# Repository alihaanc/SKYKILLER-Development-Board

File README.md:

# SKYKILLER-Development-Board
Drone and Rocket Development PCB board

## Different Color

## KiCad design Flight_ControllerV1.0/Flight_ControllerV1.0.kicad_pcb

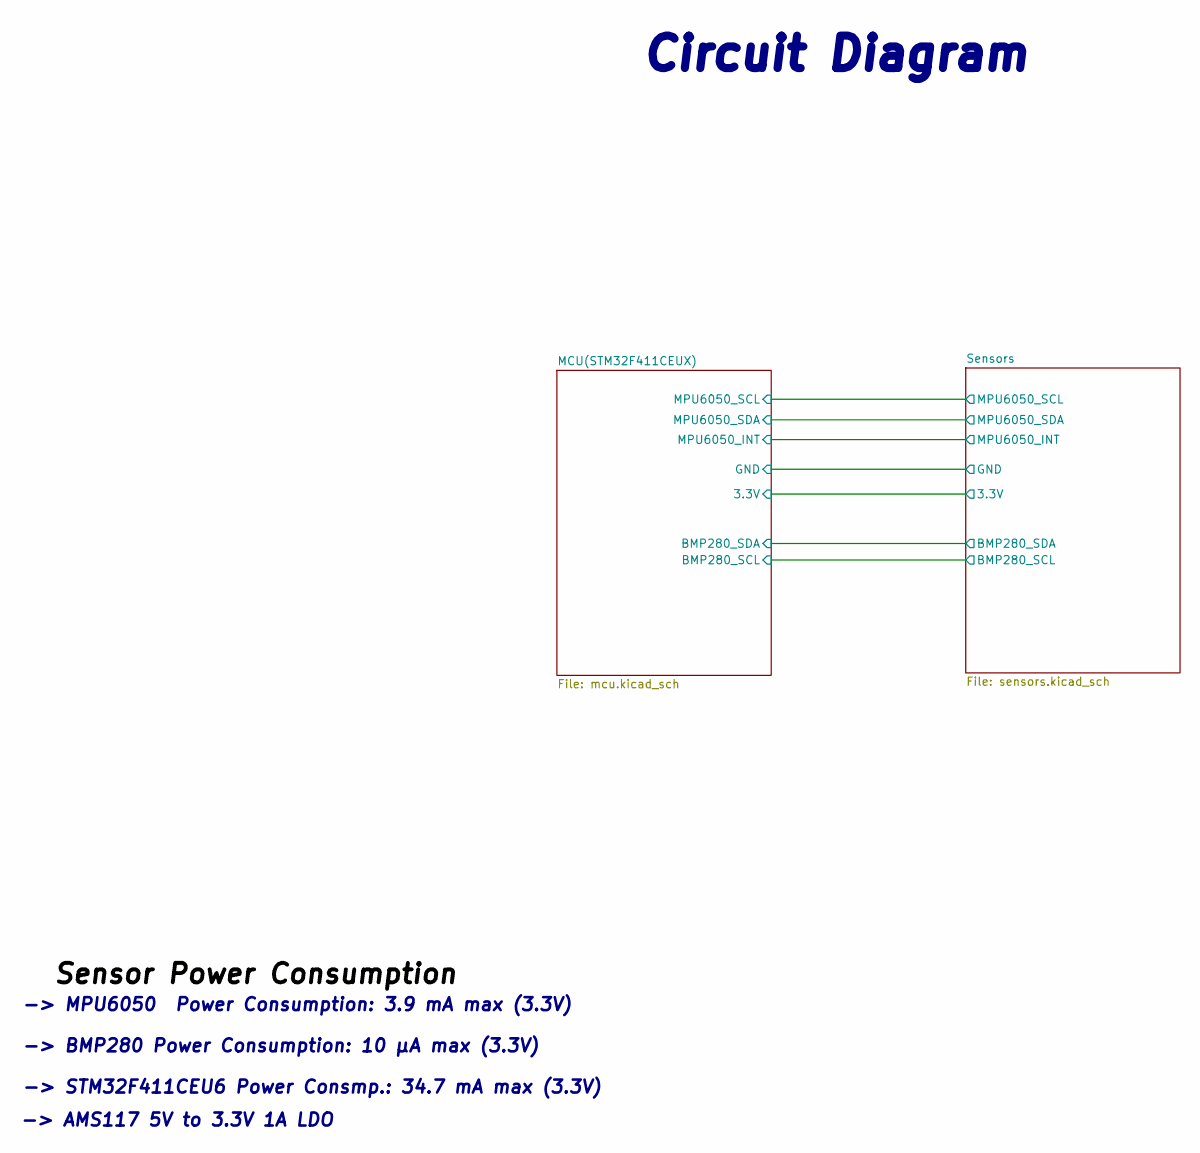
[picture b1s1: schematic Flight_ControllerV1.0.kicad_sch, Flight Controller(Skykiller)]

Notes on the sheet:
-> AMS117 5V to 3.3V 1A LDO
Circuit Diagram
-> MPU6050 Power Consumption: 3.9 mA max (3.3V)
-> BMP280 Power Consumption: 10 μA max (3.3V)
-> STM32F411CEU6 Power Consmp.: 34.7 mA max (3.3V)

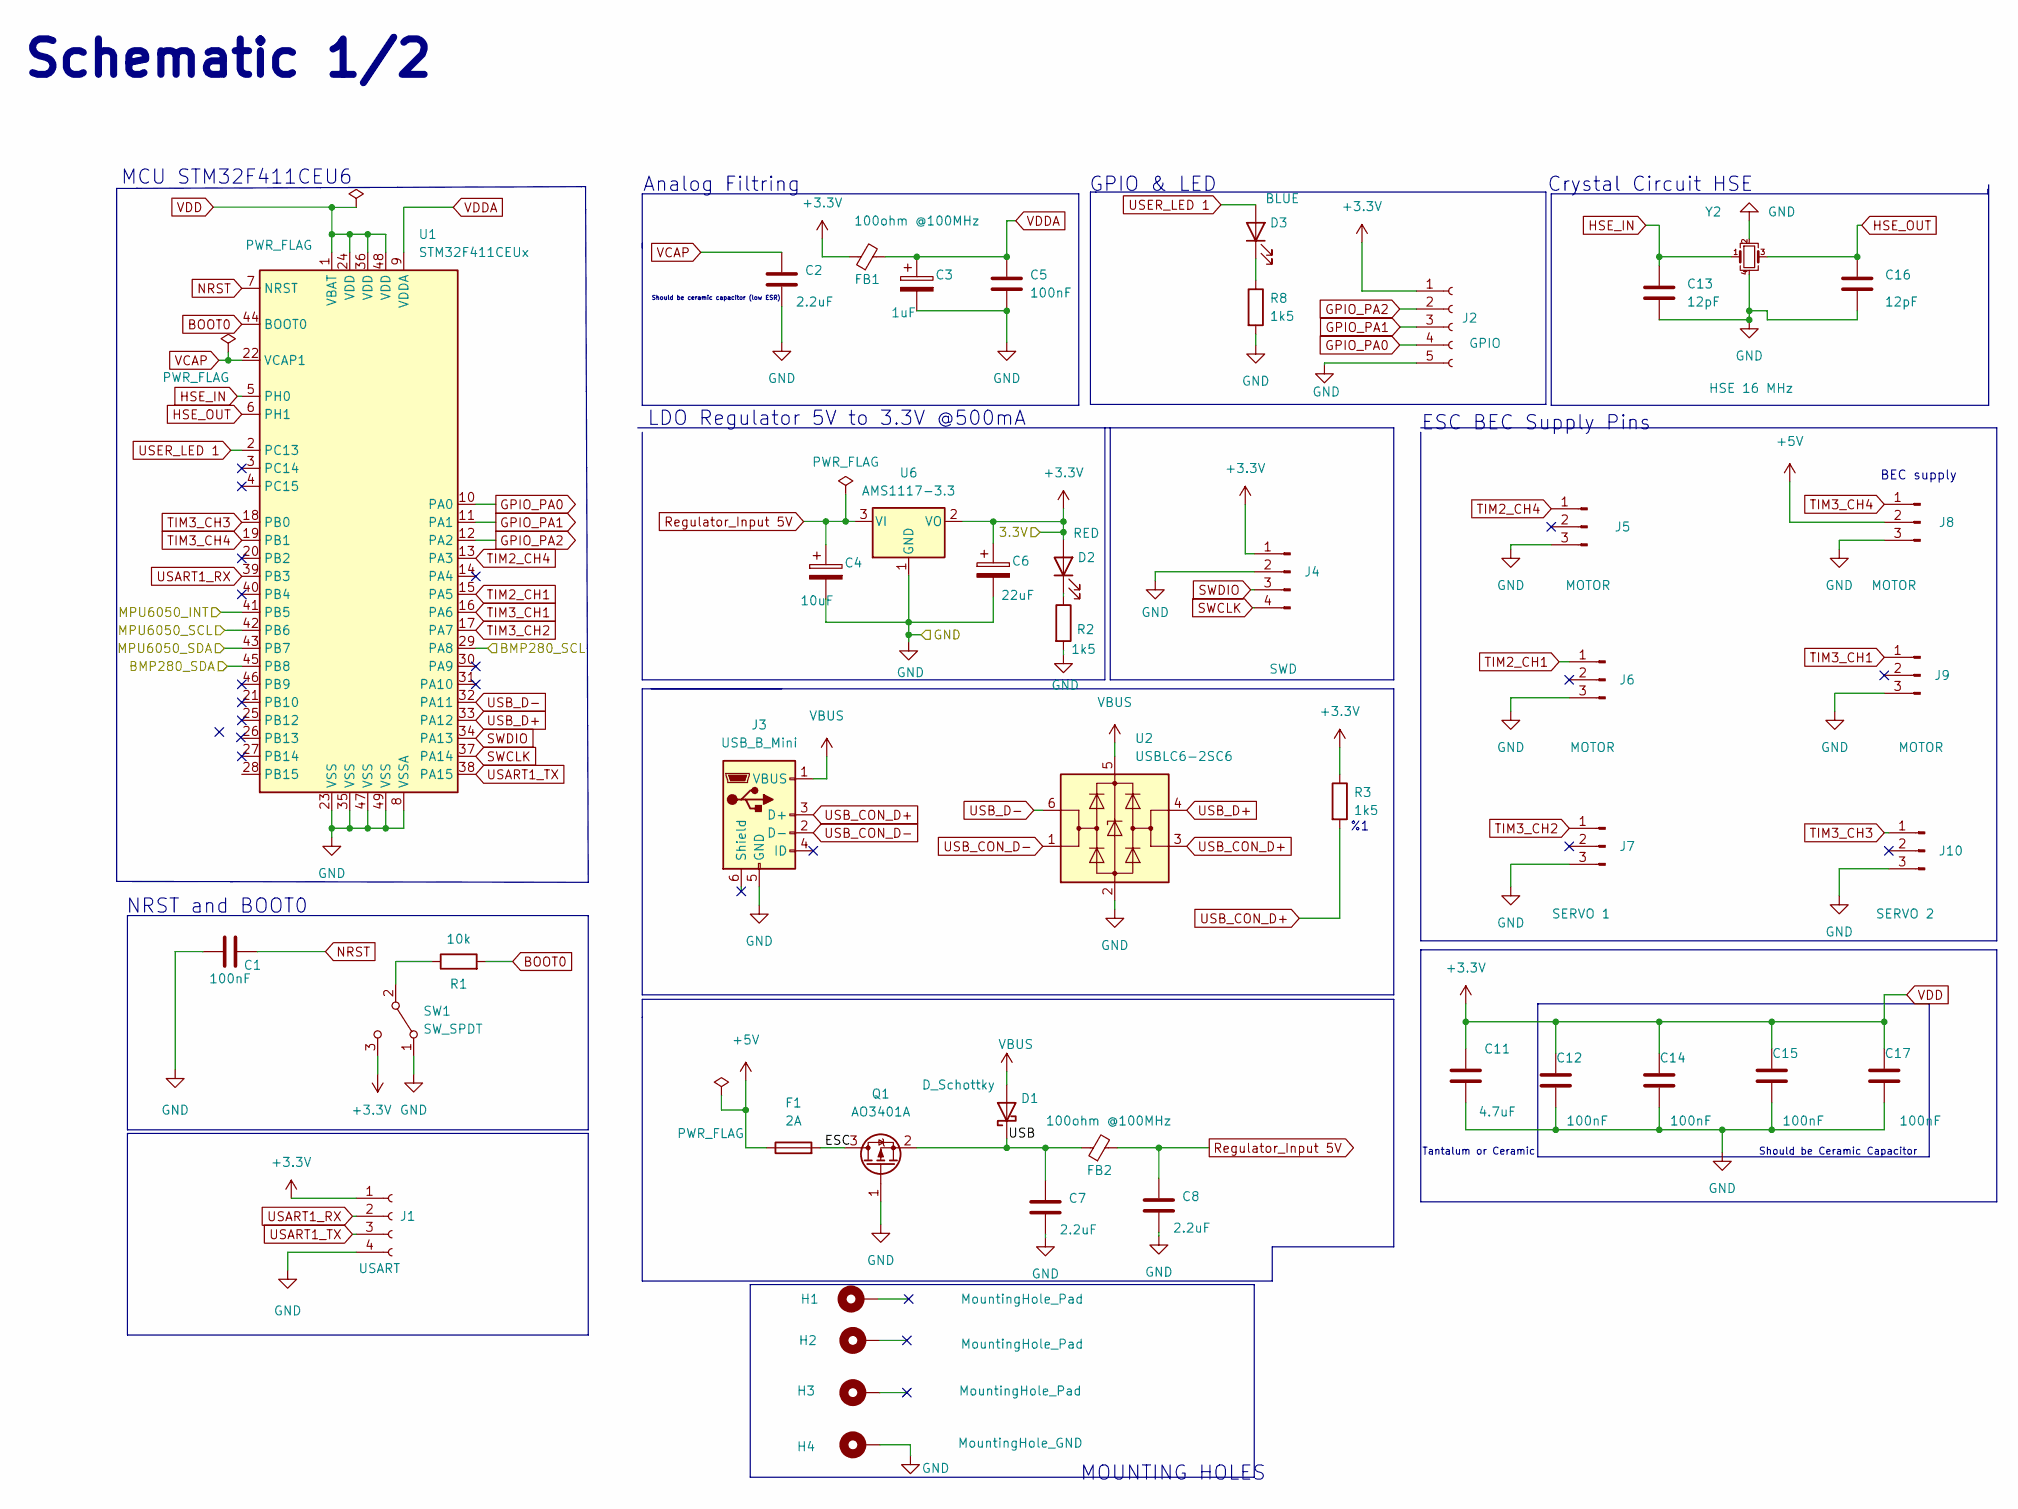
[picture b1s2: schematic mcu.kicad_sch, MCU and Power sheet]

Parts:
C1, C5, C12, C14, C15, C17: 100nF; C_0603_1608Metric
C2, C7, C8: 2.2uF; C_0603_1608Metric
C3: 1uF; CP_Elec_4x5.4
C4: 10uF; CP_Elec_4x5.4
C6: 22uF; CP_Elec_4x5.4
C11: 4.7uF; C_0603_1608Metric
C13, C16: 12pF; C_0402_1005Metric
D1: D_Schottky; D_SOD-123F
D2: RED; LED_0805_2012Metric
D3: BLUE; LED_0805_2012Metric
F1: 2A; Fuse_0603_1608Metric
FB1, FB2: 100ohm @100MHz; L_0805_2012Metric
H1, H2, H3: MountingHole_Pad; MountingHole_4.3mm_M4_Pad_Via
H4: MountingHole_GND; MountingHole_4.3mm_M4_Pad_Via
J1: USART; PinHeader_1x04_P2.54mm_Horizontal
J2: GPIO; PinHeader_1x05_P2.54mm_Horizontal
J3: USB_B_Mini; USB_Mini-B_Wuerth_65100516121_Horizontal
J4: SWD; PinHeader_1x04_P2.54mm_Vertical
J5, J6, J8, J9: MOTOR; PinHeader_1x03_P2.54mm_Vertical
J7: SERVO 1; PinHeader_1x03_P2.54mm_Vertical
J10: SERVO 2; PinHeader_1x03_P2.54mm_Vertical
Q1: AO3401A; SOT-23
R1: 10k; R_0603_1608Metric
R2, R3: 1k5; R_0201_0603Metric
R8: 1k5; R_0603_1608Metric
SW1: SW_SPDT; SW_SPDT_PCM12
U1: STM32F411CEUx; QFN-48-1EP_7x7mm_P0.5mm_EP5.6x5.6mm
U2: USBLC6-2SC6; SOT-23-6
U6: AMS1117-3.3; SOT-223-3_TabPin2
Y2: HSE 16 MHz; Crystal_SMD_3225-4Pin_3.2x2.5mm

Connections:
+3.3V: C6.1, C11.1, C12.2, C14.2, C15.2, C17.2, D2.2 (A), FB1.1, J1.1, J2.1, J4.1, R3.1, SW1.3 (C), U1.1 (VBAT), U1.24 (VDD), U1.36 (VDD), U1.48 (VDD), U6.2 (VO); also elsewhere on the board
+5V: F1.1, J8.2
/MCU(STM32F411CEUX)/BMP280_SCL: U1.29 (PA8); also elsewhere on the board
/MCU(STM32F411CEUX)/BMP280_SDA: U1.45 (PB8); also elsewhere on the board
/MCU(STM32F411CEUX)/ESC: F1.2, Q1.3 (D)
/MCU(STM32F411CEUX)/MPU6050_INT: U1.41 (PB5); also elsewhere on the board
/MCU(STM32F411CEUX)/MPU6050_SCL: U1.42 (PB6); also elsewhere on the board
/MCU(STM32F411CEUX)/MPU6050_SDA: U1.43 (PB7); also elsewhere on the board
BOOT0: R1.2, U1.44 (BOOT0)
GND: C1.1, C2.2, C3.2, C4.2, C5.2, C6.2, C7.2, C8.2, C11.2, C12.1, C13.2, C14.1, C15.1, C16.2, C17.1, H4.1, J1.4, J2.5, J3.5 (GND), J4.2, J5.3, J6.3, J7.3, J8.3, J9.3, J10.3, Q1.1 (G), R2.2, R8.2, SW1.1 (A), U1.8 (VSSA), U1.23 (VSS), U1.35 (VSS), U1.47 (VSS), U1.49 (VSS), U2.2 (GND), U6.1 (GND), Y2.2, Y2.4; also elsewhere on the board
GPIO_PA0: J2.4, U1.10 (PA0)
GPIO_PA1: J2.3, U1.11 (PA1)
GPIO_PA2: J2.2, U1.12 (PA2)
HSE_IN: C13.1, U1.5 (PH0), Y2.1
HSE_OUT: C16.1, U1.6 (PH1), Y2.3
NRST: C1.2, U1.7 (NRST)
unnamed: C7.1, D1.1 (K), FB2.1, Q1.2 (S)
unnamed: D2.1 (K), R2.1
unnamed: D3.1 (K), R8.1
unnamed: R1.1, SW1.2 (B)
Regulator_Input 5V: C4.1, C8.1, FB2.2, U6.3 (VI)
SWCLK: J4.4, U1.37 (PA14)
SWDIO: J4.3, U1.34 (PA13)
TIM2_CH1: J6.1, U1.15 (PA5)
TIM2_CH4: J5.1, U1.13 (PA3)
TIM3_CH1: J9.1, U1.16 (PA6)
TIM3_CH2: J7.1, U1.17 (PA7)
TIM3_CH3: J10.1, U1.18 (PB0)
TIM3_CH4: J8.1, U1.19 (PB1)
USART1_RX: J1.2, U1.39 (PB3)
USART1_TX: J1.3, U1.38 (PA15)
USB_CON_D+: J3.3 (D+), R3.2, U2.3 (I/O2)
USB_CON_D-: J3.2 (D-), U2.1 (I/O1)
USB_D+: U1.33 (PA12), U2.4 (I/O2)
USB_D-: U1.32 (PA11), U2.6 (I/O1)
USER_LED 1: D3.2 (A), U1.2 (PC13)
VBUS: D1.2 (A), J3.1 (VBUS), U2.5 (VBUS)
VCAP: C2.1, U1.22 (VCAP1)
VDDA: C3.1, C5.1, FB1.2, U1.9 (VDDA)

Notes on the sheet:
ESC BEC Supply Pins
BEC supply
Should be Ceramic Capacitor
Tantalum or Ceramic
GPIO & LED
Should be ceramic capacitor (low ESR)
MCU STM32F411CEU6
MOUNTING HOLES
Crystal Circuit HSE
LDO Regulator 5V to 3.3V @500mA
Analog Filtring
Schematic 1/2
NRST and BOOT0

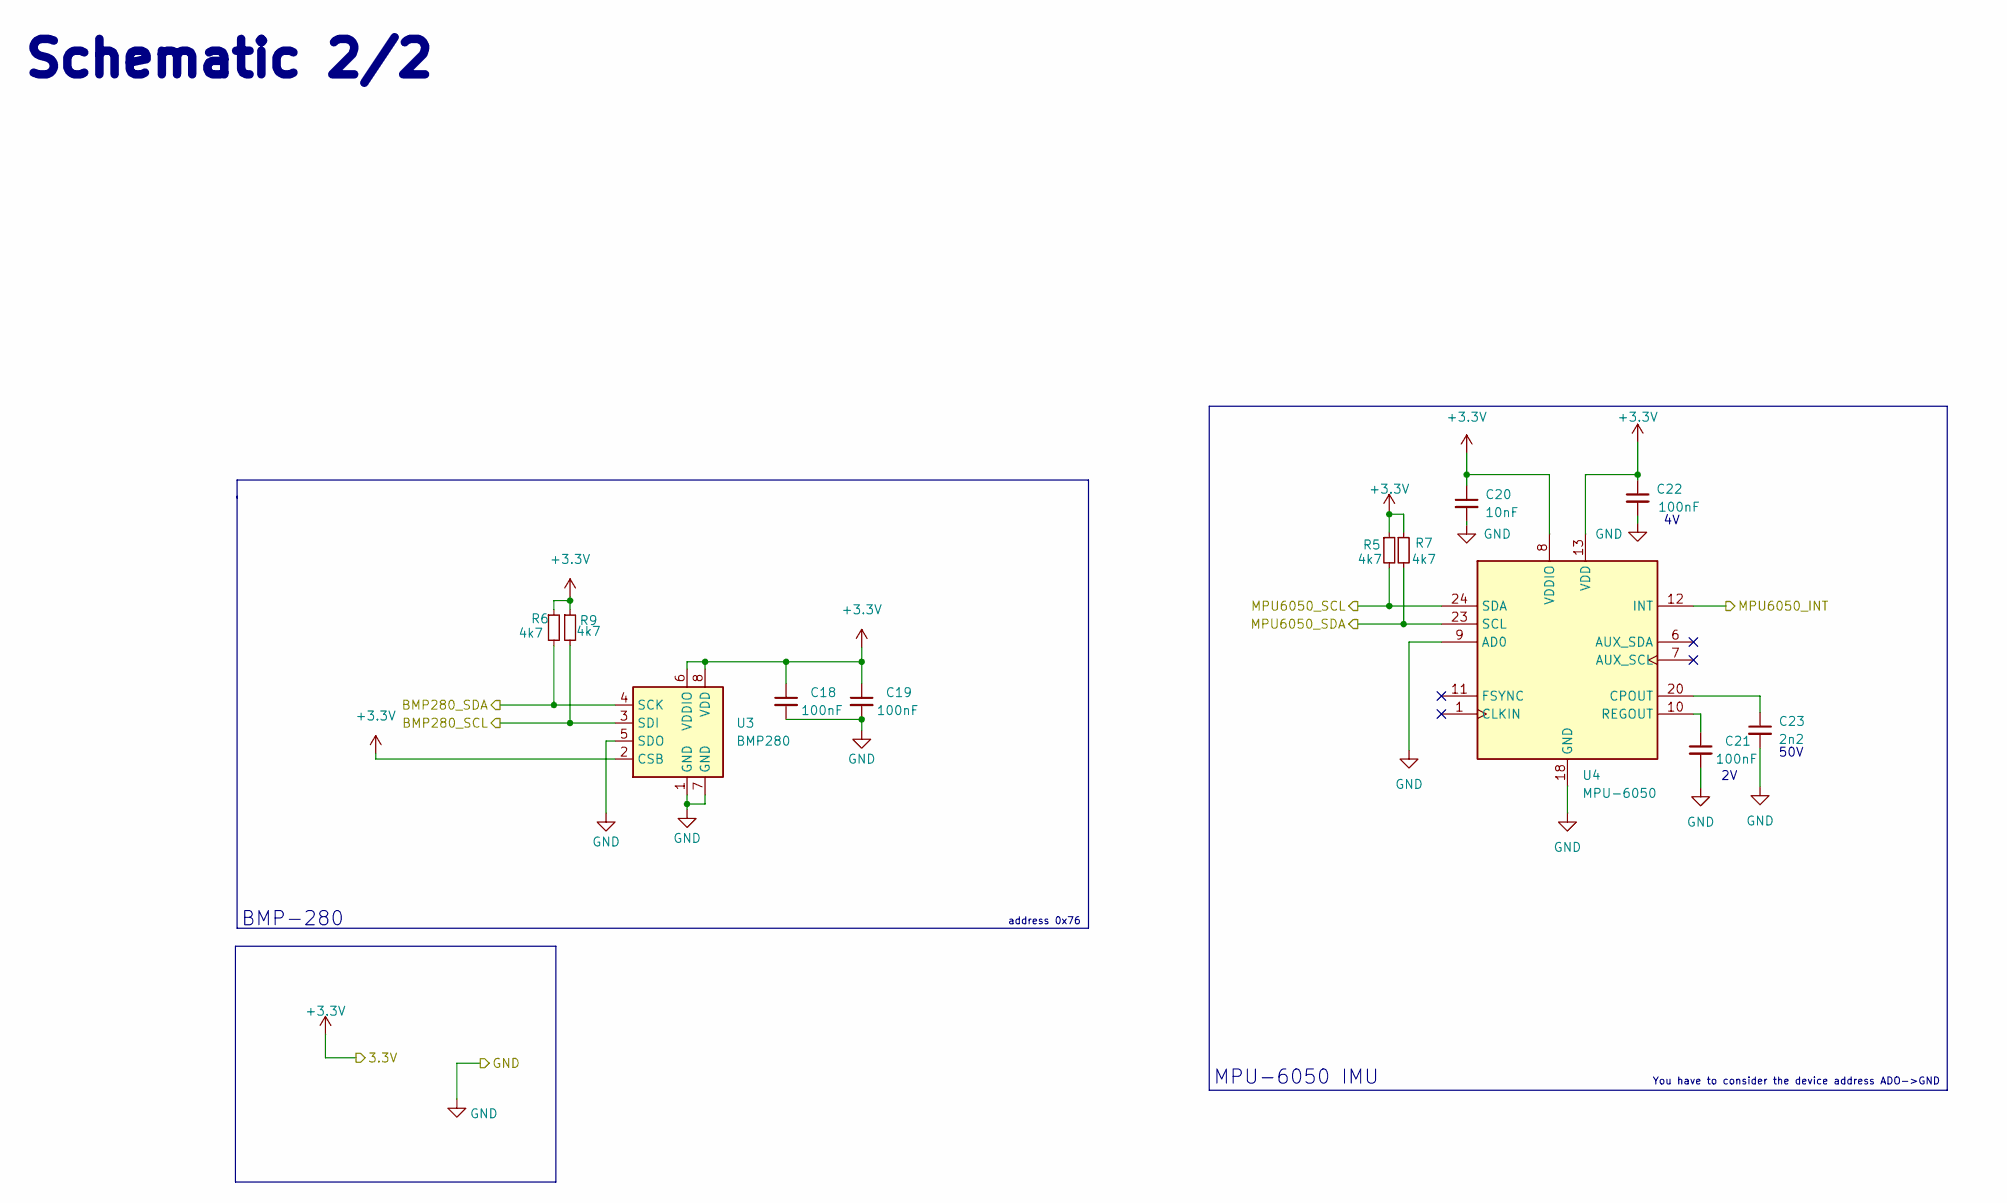
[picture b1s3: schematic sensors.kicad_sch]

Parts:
C18, C19, C21, C22: 100nF; C_0603_1608Metric
C20: 10nF; C_0402_1005Metric
C23: 2n2; C_0603_1608Metric
R5, R6, R7, R9: 4k7; R_0603_1608Metric
U3: BMP280; Bosch_LGA-8_2x2.5mm_P0.65mm_ClockwisePinNumbering
U4: MPU-6050; InvenSense_QFN-24_4x4mm_P0.5mm

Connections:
+3.3V: C18.1, C19.1, C20.1, C22.1, R5.1, R6.1, R7.1, R9.1, U3.2 (CSB), U3.6 (VDDIO), U3.8 (VDD), U4.8 (VDDIO), U4.13 (VDD); also elsewhere on the board
/MCU(STM32F411CEUX)/BMP280_SCL: R9.2, U3.3 (SDI); also elsewhere on the board
/MCU(STM32F411CEUX)/BMP280_SDA: R6.2, U3.4 (SCK); also elsewhere on the board
/MCU(STM32F411CEUX)/MPU6050_INT: U4.12 (INT); also elsewhere on the board
/MCU(STM32F411CEUX)/MPU6050_SCL: R5.2, U4.24 (SDA); also elsewhere on the board
/MCU(STM32F411CEUX)/MPU6050_SDA: R7.2, U4.23 (SCL); also elsewhere on the board
GND: C18.2, C19.2, C20.2, C21.2, C22.2, C23.2, U3.1 (GND), U3.5 (SDO), U3.7 (GND), U4.9 (AD0), U4.18 (GND); also elsewhere on the board
unnamed: C21.1, U4.10 (REGOUT)
unnamed: C23.1, U4.20 (CPOUT)

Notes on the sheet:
Schematic 2/2
address 0x76
BMP-280
50V
You have to consider the device address ADO->GND
MPU-6050 IMU

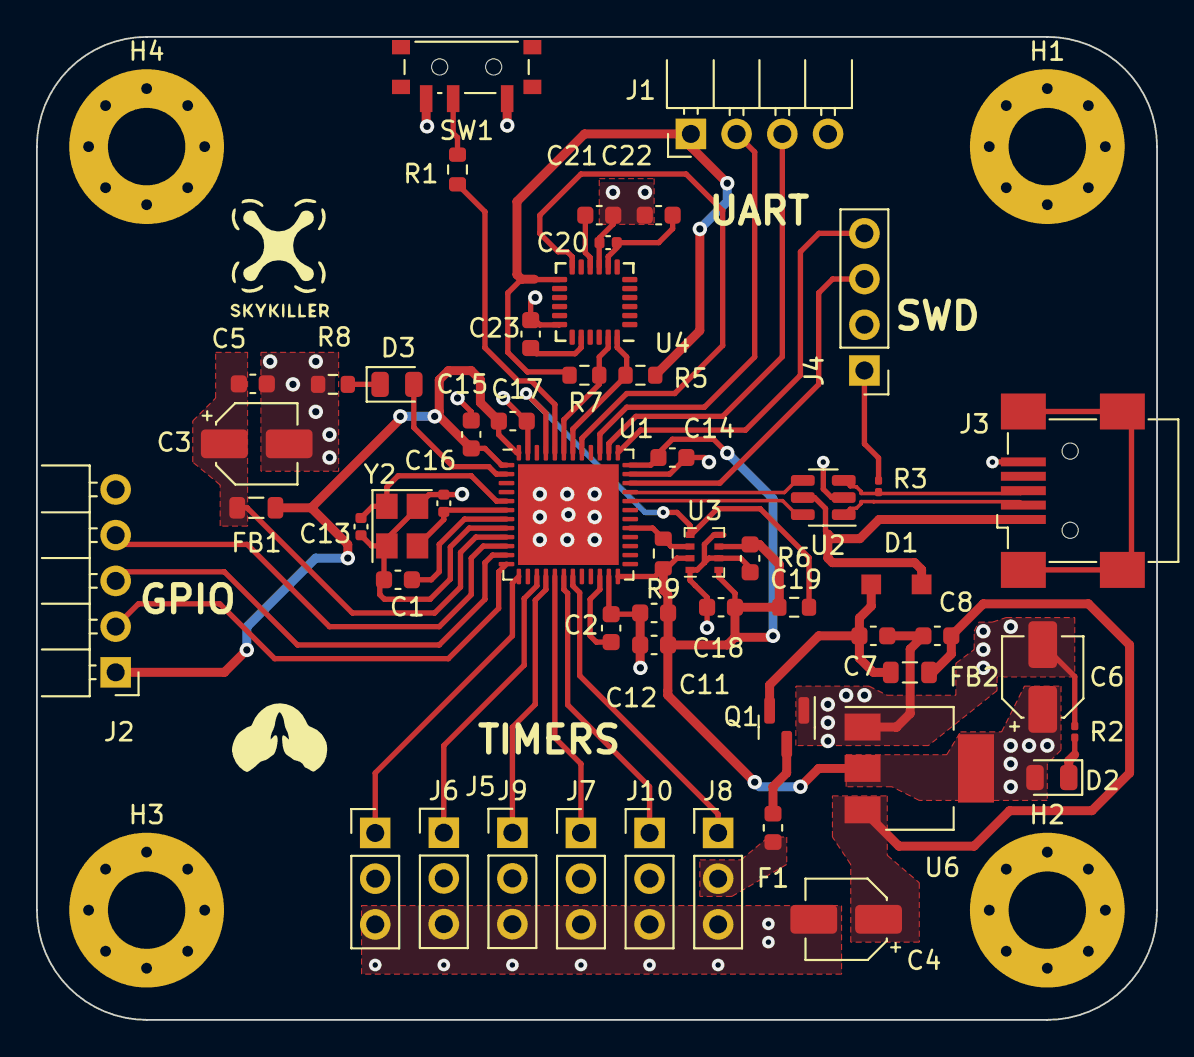
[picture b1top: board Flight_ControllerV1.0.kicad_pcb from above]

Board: 4 copper layers, 62.2 x 54.6 mm, 57 parts (0 on the bottom side), 41 nets.

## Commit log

2023-02-16 Development Board
